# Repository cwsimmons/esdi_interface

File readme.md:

# A Zynq Based ESDI Disk Interface

The immediate goal of this project is to create a solution for reading data off old ESDI hard drives. At the moment it is capable of reading disk formatted by a couple of controllers, with retry logic, to create an image. More work needs to be done to increase confidence in its results.

I have made a PCB which allows me to connect a drive to my dev kit. It is an FMC based design, so unfortunately it only connects to dev boards which are over kill for this application. Nevertheless, the design files can be found under `esdi_fmc`
Eventually, I'd like to create a PCB that can accompany a cheaper (hopefully significantly) dev board than the one I'm using. In the meantime, someone with prior Zynq experience should not have much trouble moving the design to a different board.

### Todo:
* Read the defect table
* Add support for more formats.
* Make sector timings more dynamic/adaptive. At the very least it needs to consider the drive's data rate.
* Figure out an abstracted way to handle relocated sectors.

## License

This program is free software: you can redistribute it and/or modify it under the terms of the GNU General Public License as published by the Free Software Foundation, either version 2 of the License, or (at your option) any later version.

This program is distributed in the hope that it will be useful, but WITHOUT ANY WARRANTY; without even the implied warranty of MERCHANTABILITY or FITNESS FOR A PARTICULAR PURPOSE. See the GNU General Public License for more details.

You should have received a copy of the GNU General Public License along with this program. If not, see <https://www.gnu.org/licenses/>.

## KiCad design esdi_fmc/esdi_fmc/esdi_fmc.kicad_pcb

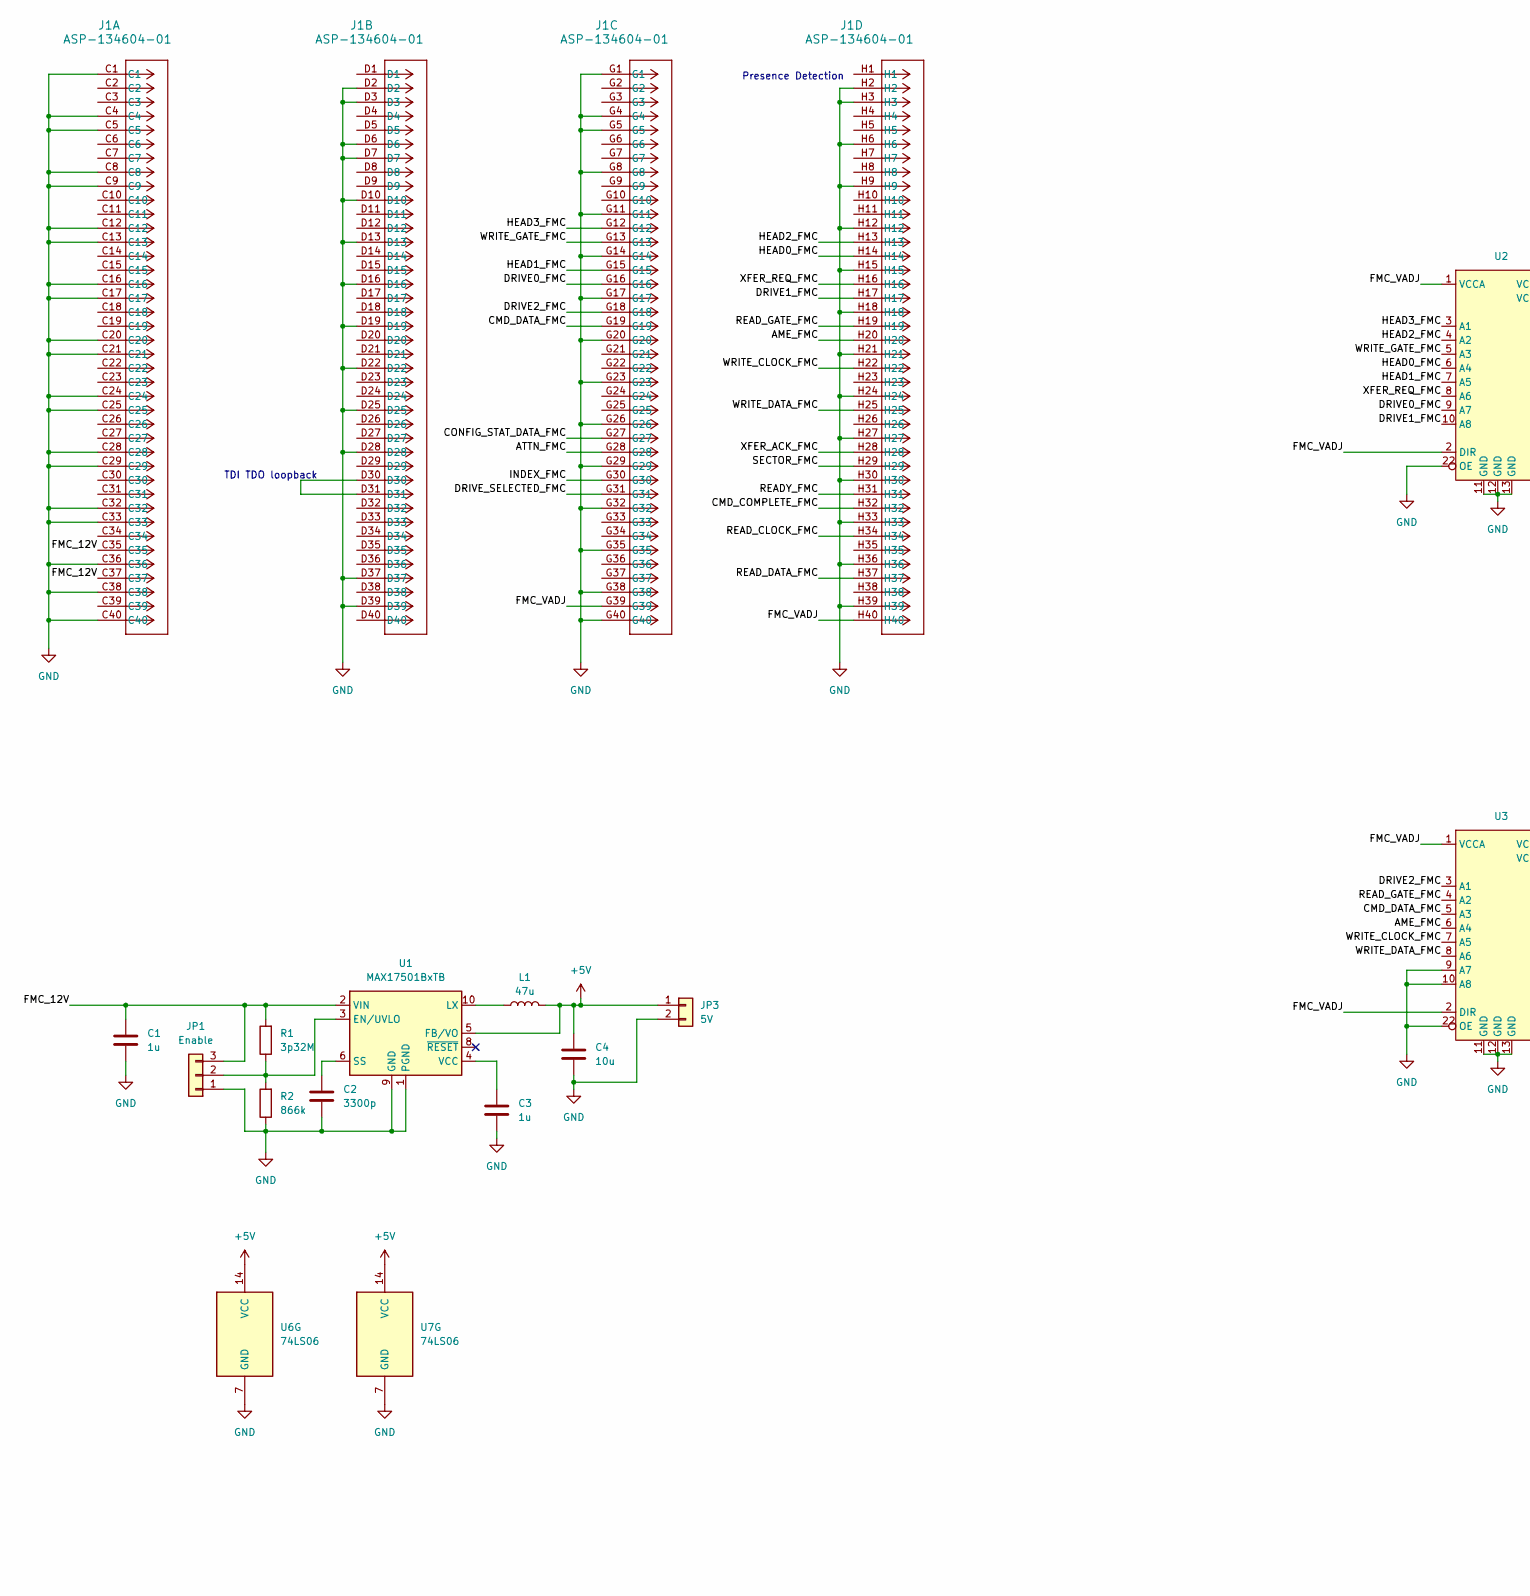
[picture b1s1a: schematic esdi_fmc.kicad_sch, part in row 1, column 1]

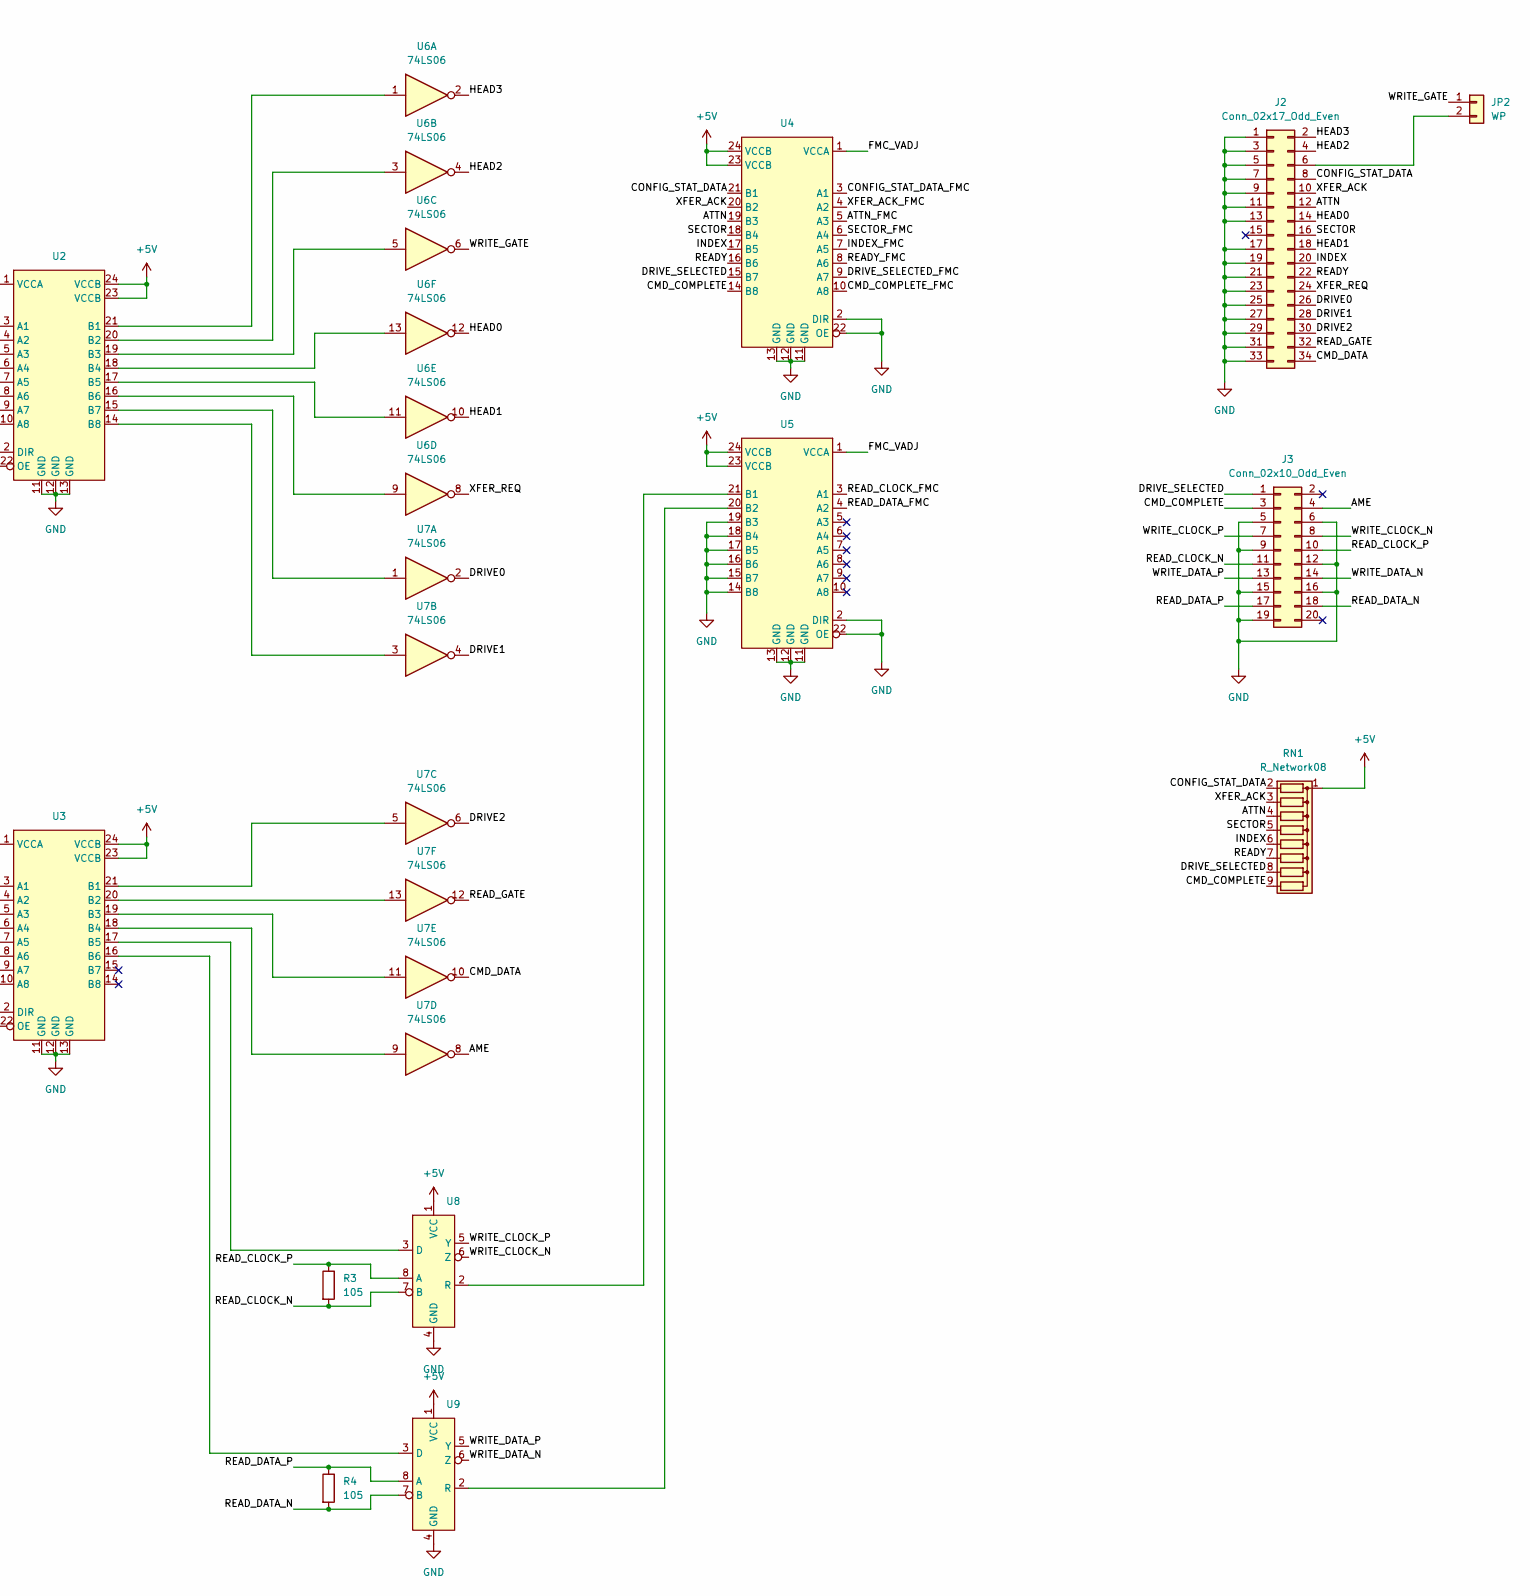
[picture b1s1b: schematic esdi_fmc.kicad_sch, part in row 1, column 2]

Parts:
C1, C3: 1u; C_1206_3216Metric
C2: 3300p; C_1206_3216Metric
C4: 10u; C_1206_3216Metric
J1: ASP-134604-01; CONN_ASP-134604-01_SAI
J2: Conn_02x17_Odd_Even; PinHeader_2x17_P2.54mm_Vertical
J3: Conn_02x10_Odd_Even; PinHeader_2x10_P2.54mm_Vertical
JP1: Enable; PinHeader_1x03_P2.54mm_Vertical
JP2: WP; PinHeader_1x02_P2.54mm_Vertical
JP3: 5V; PinHeader_1x02_P2.54mm_Vertical
L1: 47u; Inductor_Eaton_SD53
R1: 3p32M; R_0805_2012Metric
R2: 866k; R_0805_2012Metric
R3, R4: 105; R_0805_2012Metric
RN1: R_Network08; R_Array_SIP9
U1: MAX17501BxTB; TDFN-10-1EP_2x3mm_P0.5mm_EP0.9x2mm
U2, U3, U4, U5: TSSOP-24_4.4x7.8mm_P0.65mm
U6, U7: 74LS06; SOIC-14_3.9x8.7mm_P1.27mm
U8, U9: SOIC-8_3.9x4.9mm_P1.27mm

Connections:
+5V: C4.1, JP3.1, L1.2, RN1.1 (common), U1.5 (FB/VO), U2.23 (VCCB), U2.24 (VCCB), U3.23 (VCCB), U3.24 (VCCB), U4.23 (VCCB), U4.24 (VCCB), U5.23 (VCCB), U5.24 (VCCB), U6.14 (VCC), U7.14 (VCC), U8.1 (VCC), U9.1 (VCC)
/AME: J3.4, U7.8
/AME_FMC: J1.H20, U3.6 (A4)
/ATTN: J2.12, RN1.4 (R3), U4.19 (B3)
/ATTN_FMC: J1.G28, U4.5 (A3)
/CMD_COMPLETE: J3.3, RN1.9 (R8), U4.14 (B8)
/CMD_COMPLETE_FMC: J1.H32, U4.10 (A8)
/CMD_DATA: J2.34, U7.10
/CMD_DATA_FMC: J1.G19, U3.5 (A3)
/CONFIG_STAT_DATA: J2.8, RN1.2 (R1), U4.21 (B1)
/CONFIG_STAT_DATA_FMC: J1.G27, U4.3 (A1)
/DRIVE0: J2.26, U7.2
/DRIVE0_FMC: J1.G16, U2.9 (A7)
/DRIVE1: J2.28, U7.4
/DRIVE1_FMC: J1.H17, U2.10 (A8)
/DRIVE2: J2.30, U7.6
/DRIVE2_FMC: J1.G18, U3.3 (A1)
/DRIVE_SELECTED: J3.1, RN1.8 (R7), U4.15 (B7)
/DRIVE_SELECTED_FMC: J1.G31, U4.9 (A7)
/FMC_12V: C1.1, J1.C35, J1.C37, JP1.3, R1.2, U1.2 (VIN)
/FMC_VADJ: J1.G39, J1.H40, U2.1 (VCCA), U2.2 (DIR), U3.1 (VCCA), U3.2 (DIR), U4.1 (VCCA), U5.1 (VCCA)
/HEAD0: J2.14, U6.12
/HEAD0_FMC: J1.H14, U2.6 (A4)
/HEAD1: J2.18, U6.10
/HEAD1_FMC: J1.G15, U2.7 (A5)
/HEAD2: J2.4, U6.4
/HEAD2_FMC: J1.H13, U2.4 (A2)
/HEAD3: J2.2, U6.2
/HEAD3_FMC: J1.G12, U2.3 (A1)
/INDEX: J2.20, RN1.6 (R5), U4.17 (B5)
/INDEX_FMC: J1.G30, U4.7 (A5)
/READY: J2.22, RN1.7 (R6), U4.16 (B6)
/READY_FMC: J1.H31, U4.8 (A6)
/READ_CLOCK_FMC: J1.H34, U5.3 (A1)
/READ_CLOCK_N: J3.11, R3.2, U8.7 (B)
/READ_CLOCK_P: J3.10, R3.1, U8.8 (A)
/READ_DATA_FMC: J1.H37, U5.4 (A2)
/READ_DATA_N: J3.18, R4.2, U9.7 (B)
/READ_DATA_P: J3.17, R4.1, U9.8 (A)
/READ_GATE: J2.32, U7.12
/READ_GATE_FMC: J1.H19, U3.4 (A2)
/SECTOR: J2.16, RN1.5 (R4), U4.18 (B4)
/SECTOR_FMC: J1.H29, U4.6 (A4)
/WRITE_CLOCK_FMC: J1.H22, U3.7 (A5)
/WRITE_CLOCK_N: J3.8, U8.6 (Z)
/WRITE_CLOCK_P: J3.7, U8.5 (Y)
/WRITE_DATA_FMC: J1.H25, U3.8 (A6)
/WRITE_DATA_N: J3.14, U9.6 (Z)
/WRITE_DATA_P: J3.13, U9.5 (Y)
/WRITE_GATE: JP2.1, U6.6
/WRITE_GATE_FMC: J1.G13, U2.5 (A3)
/XFER_ACK: J2.10, RN1.3 (R2), U4.20 (B2)
/XFER_ACK_FMC: J1.H28, U4.4 (A2)
/XFER_REQ: J2.24, U6.8
/XFER_REQ_FMC: J1.H16, U2.8 (A6)
GND: C1.2, C2.2, C3.2, C4.2, J1.C1, J1.C4, J1.C5, J1.C8, J1.C9, J1.C12, J1.C13, J1.C16, J1.C17, J1.C20, J1.C21, J1.C24, J1.C25, J1.C28, J1.C29, J1.C32, J1.C33, J1.C36, J1.C38, J1.C40, J1.D2, J1.D3, J1.D6, J1.D7, J1.D10, J1.D13, J1.D16, J1.D19, J1.D22, J1.D25, J1.D28, J1.D37, J1.D39, J1.G1, J1.G4, J1.G5, J1.G8, J1.G11, J1.G14, J1.G17, J1.G20, J1.G23, J1.G26, J1.G29, J1.G32, J1.G35, J1.G38, J1.G40, J1.H2, J1.H3, J1.H6, J1.H9, J1.H12, J1.H15, J1.H18, J1.H21, J1.H24, J1.H27, J1.H30, J1.H33, J1.H36, J1.H39, J2.1, J2.3, J2.5, J2.7, J2.9, J2.11, J2.13, J2.17, J2.19, J2.21, J2.23, J2.25, J2.27, J2.29, J2.31, J2.33, J3.5, J3.6, J3.9, J3.12, J3.15, J3.16, J3.19, JP1.1, JP3.2, R2.1, U1.1 (PGND), U1.9 (GND), U1.11 (GND), U2.11 (GND), U2.12 (GND), U2.13 (GND), U2.22 (OE), U3.9 (A7), U3.10 (A8), U3.11 (GND), U3.12 (GND), U3.13 (GND), U3.22 (OE), U4.2 (DIR), U4.11 (GND), U4.12 (GND), U4.13 (GND), U4.22 (OE), U5.2 (DIR), U5.11 (GND), U5.12 (GND), U5.13 (GND), U5.14 (B8), U5.15 (B7), U5.16 (B6), U5.17 (B5), U5.18 (B4), U5.19 (B3), U5.22 (OE), U6.7 (GND), U7.7 (GND), U8.4 (GND), U9.4 (GND)
unnamed: J1.D30, J1.D31
unnamed: J2.6, JP2.2
unnamed: JP1.2, R1.1, R2.2, U1.3 (EN/UVLO)
unnamed: L1.1, U1.10 (LX)
unnamed: C2.1, U1.6 (SS)
unnamed: C3.1, U1.4 (VCC)
unnamed: U2.21 (B1), U6.1
unnamed: U2.20 (B2), U6.3
unnamed: U2.19 (B3), U6.5
unnamed: U2.18 (B4), U6.13
unnamed: U2.17 (B5), U6.11
unnamed: U2.16 (B6), U6.9
unnamed: U2.15 (B7), U7.1
unnamed: U2.14 (B8), U7.3
unnamed: U3.21 (B1), U7.5
unnamed: U3.20 (B2), U7.13
unnamed: U3.19 (B3), U7.11
unnamed: U3.18 (B4), U7.9
unnamed: U3.17 (B5), U8.3 (D)
unnamed: U3.16 (B6), U9.3 (D)
unnamed: U5.21 (B1), U8.2 (R)
unnamed: U5.20 (B2), U9.2 (R)

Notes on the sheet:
TDI TDO loopback
Presence Detection

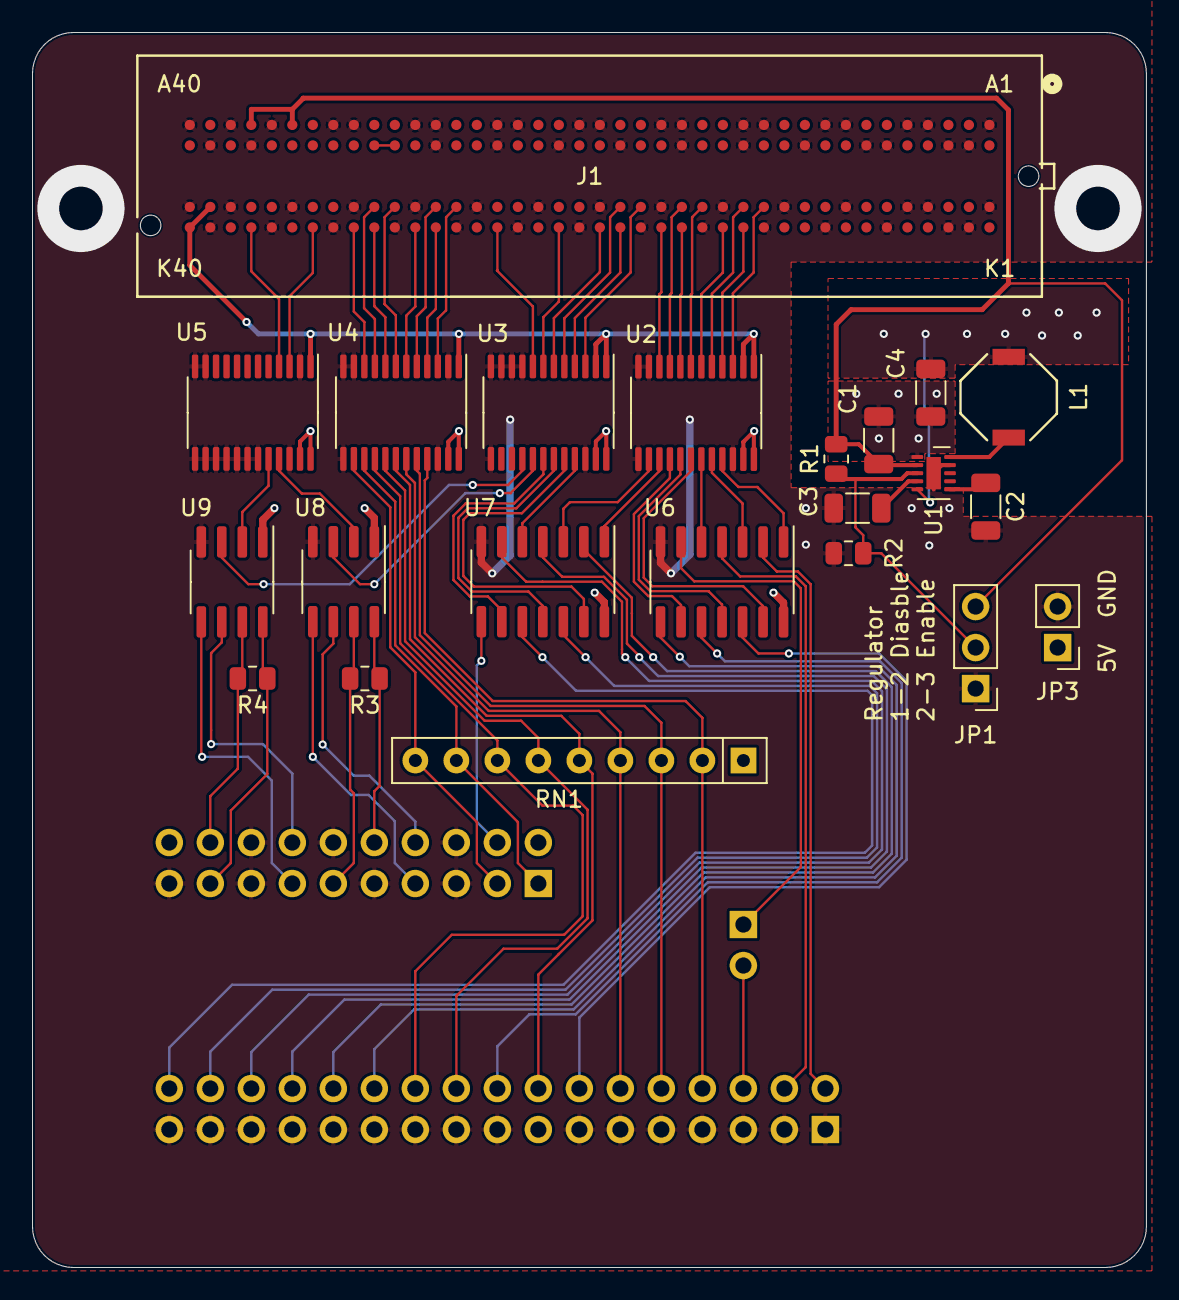
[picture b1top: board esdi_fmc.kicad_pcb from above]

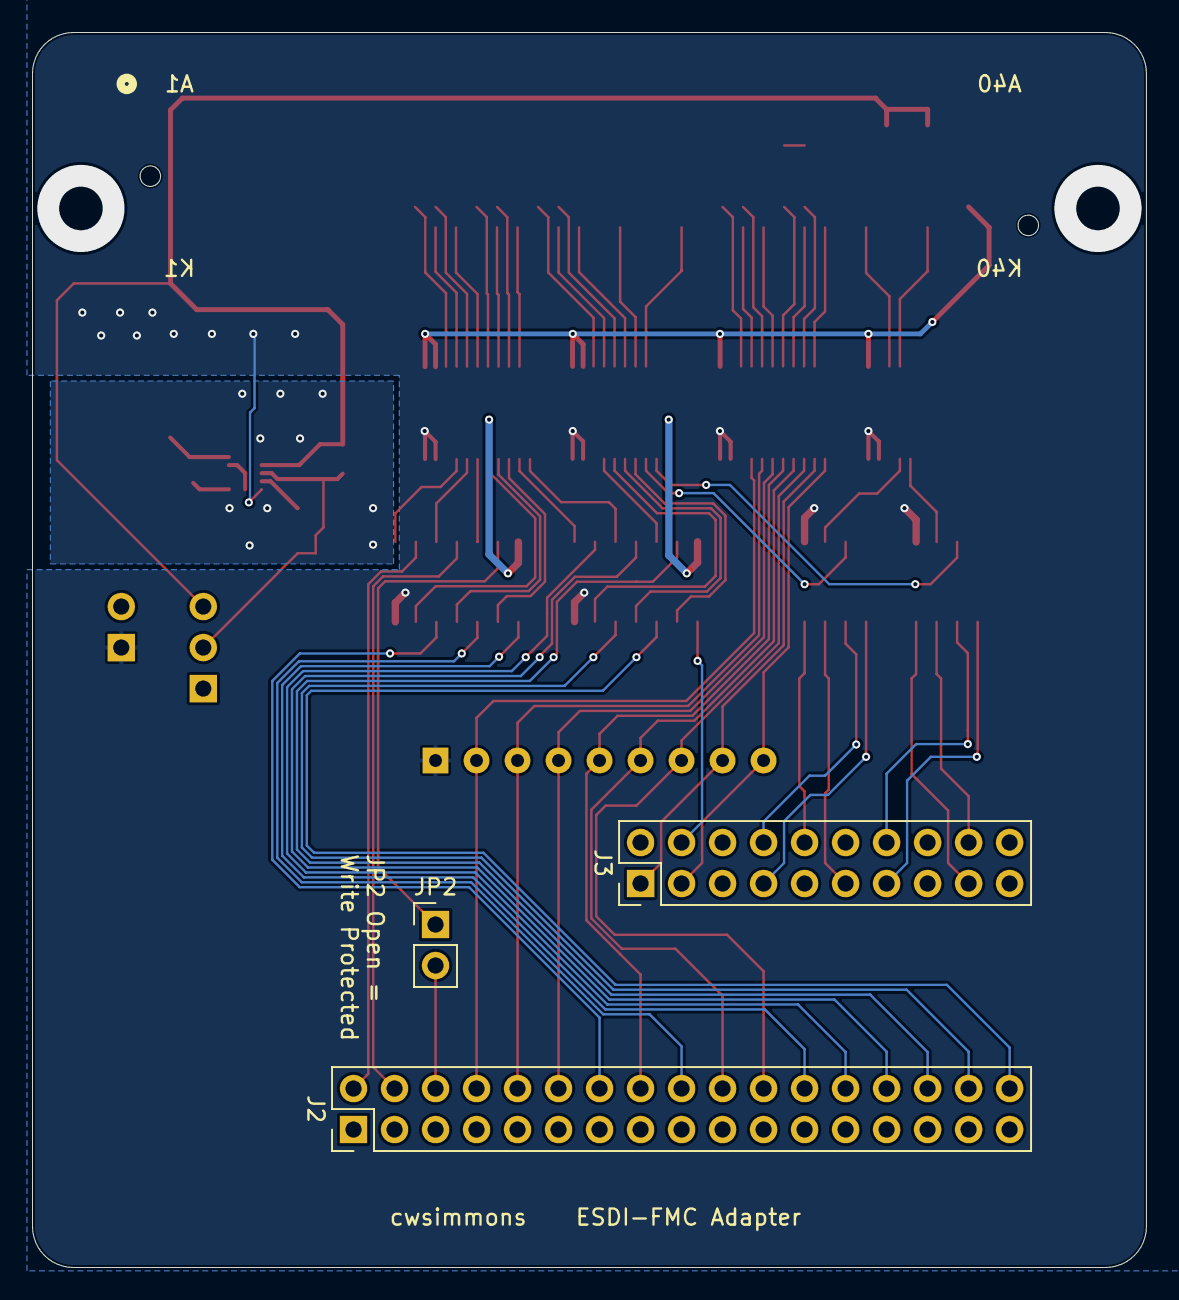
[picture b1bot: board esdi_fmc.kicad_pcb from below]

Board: 2 copper layers, 69.0 x 76.5 mm, 25 parts (3 on the bottom side), 78 nets.

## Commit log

2024-03-03 Initial AXI4 lite peripheral
2024-03-03 Add Vivado project
2024-03-03 Work on serial command interface
2024-03-03 Update parameters with slower control signal timing
2024-03-03 Add simple testbench for control signals module
2024-03-05 something something metastability
2024-03-12 Add module for asserting read gate at the right time
2024-03-12 First cut at Rx datapath
2024-03-13 Add tlast to the read datapath
2024-03-15 Bug fix from simulation
2024-03-15 Add rx datapath and dma to BD
2024-03-16 Add slapdash test code for reference
2024-03-23 Add registers for data area read gate assert/deassert times
2024-03-31 Add logic so we can read specific sectors, add fifo to bd, update constraints
2024-04-03 Add head & drive select to registers, fix rx datapath tlast issue
2024-04-03 Update experimental code
2024-04-22 Update test code for mystery soft sectored disk
2024-04-22 Add soft sectoring support
2024-06-13 Add proper software
2024-06-14 Add IBM RT controller
2024-06-14 Add readme and license
2024-06-25 Configure DMA for scatter/gather, increase BRAM
2024-06-25 Update software to use scatter/gather DMA
2024-06-28 Sector Timer: Add filter and fix bug where we could think we reached a sector even though we missed the start of it
2024-07-02 Fix bug where integer wraparound was expected but did not occur
2024-07-02 Fix the DMA reset function and add a way to clear the AXI Stream FIFO
2024-07-02 Add more cli options
2024-07-02 Update readme and util script
2024-07-02 Add Ultastor 12F controller
2024-08-06 Add cli option for drive select
2024-08-06 Add help text when controller is not specified properly
2024-08-06 Separately keep track of whether the address/data areas were read from the disk, that way we can process an address even if the data was bad
2024-08-06 Add controller IBM 5364
2024-08-06 Add more insight on the IBM PS2 controller
2024-08-30 HDL update for FMC card
2024-08-30 Add KiCad for FMC Adpater
2024-10-18 Add logic where the software resets the DMA when it appears that the fifo overflowed
2024-10-18 Add Adaptec ACB-2322
2024-10-18 Bug fix for controllers which have different sized CRC/ECC in the data area
2024-10-18 Fix logic for determing if additional attempts are needed
2024-10-18 Adaptec update
2024-10-18 Add utility program for changing the apparent sectors and heads of an image
2025-05-18 Regen TCL since it seemed to be broken somehow, also added detection for datapath overflow, and the ability determine number of sectors by counting the pulses on the sector line
2025-05-18 Remove dcp from tcl
2025-05-18 * Add timeouts wherever needed * Make DMA reset actually work * Move back data area in BRAM so that we can fit more than 128 DMA descriptors * Correct issues with 5364 code (0 based sector numbers an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
2025-07-06 Add adbility to create an emulation file
2025-08-18 Add Zedboard option
2025-12-31 Improve writing of emulation files and ability to read in emulation files and dump the data
